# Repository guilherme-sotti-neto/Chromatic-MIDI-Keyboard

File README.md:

# Chromatic MIDI Button Keyboard 

# About 
This project was made to be open for anyone who wants to make their own Chromatic MIDI Keyboard at home. 
I tried to make it as reliable and fixable as possible.

# Components 
- 1 Arduino Leonardo
- 3 1/4W 220 ohm Resistor
- 3 Buttons 
- 51 Diodes 1N4148 (I recommend them because they are very cheap and overkill for this project)
- 99 MX Hotswap Sockets
- 99 MX 5 Pins Silver Mechanical Switches

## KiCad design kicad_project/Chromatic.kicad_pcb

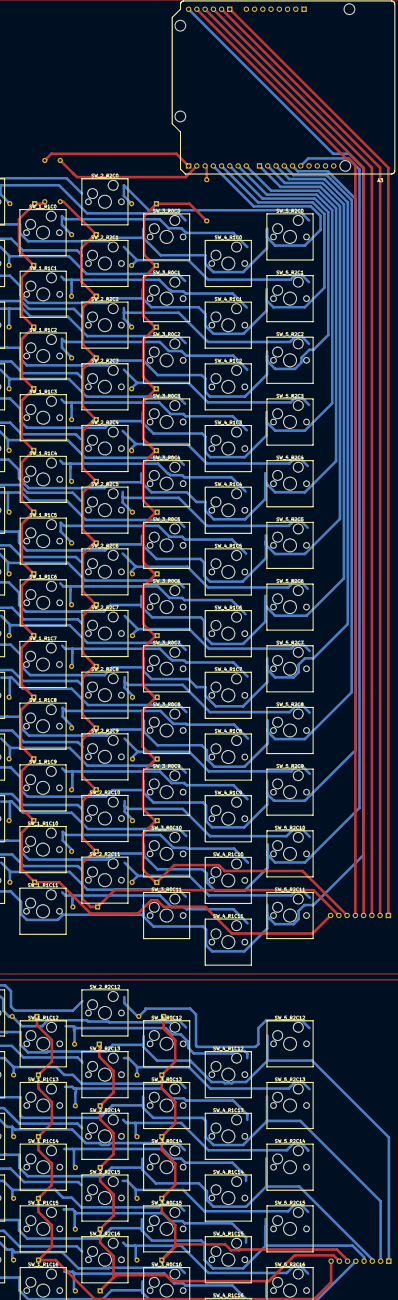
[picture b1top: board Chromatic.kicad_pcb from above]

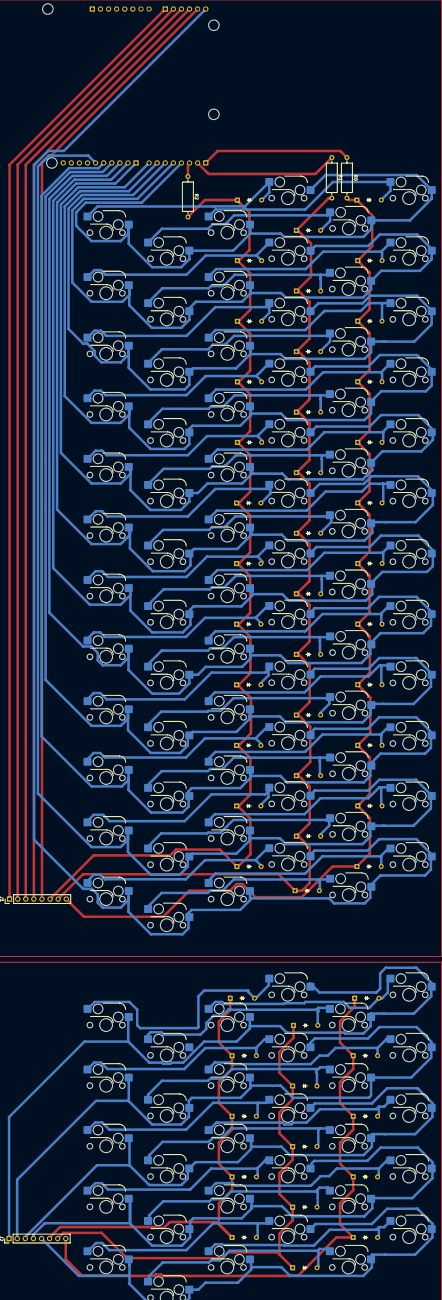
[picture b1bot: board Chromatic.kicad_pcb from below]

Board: 2 copper layers, 159 parts (56 on the bottom side), 82 nets.

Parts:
A3: Arduino_Leonardo_Shield; ARDUINO_A000066
D_R0C0, D_R0C1, D_R0C2, D_R0C3, D_R0C4, D_R0C5, D_R0C6, D_R0C7, D_R0C8, D_R0C9, D_R0C10, D_R0C11, D_R0C12, D_R0C13, D_R0C14, D_R0C15, D_R0C16, D_R1C0, D_R1C1, D_R1C2, D_R1C3, D_R1C4, D_R1C5, D_R1C6, D_R1C7, D_R1C8, D_R1C9, D_R1C10, D_R1C11, D_R1C12, D_R1C13, D_R1C14, D_R1C15, D_R1C16, D_R2C0, D_R2C1, D_R2C2, D_R2C3, D_R2C4, D_R2C5, D_R2C6, D_R2C7, D_R2C8, D_R2C9, D_R2C10, D_R2C11, D_R2C12, D_R2C13, D_R2C14, D_R2C15, D_R2C16: Diode_DO-35
J1: J1; PinHeader_1x08_P2.54mm_Vertical
J2: J2; PinHeader_1x08_P2.54mm_Vertical
R0, R1, R2: Resistor; R_Axial_DIN0309_L9.0mm_D3.2mm_P12.70mm_Horizontal
SW_0_R0C0, SW_0_R0C1, SW_0_R0C2, SW_0_R0C3, SW_0_R0C4, SW_0_R0C5, SW_0_R0C6, SW_0_R0C7, SW_0_R0C8, SW_0_R0C9, SW_0_R0C10, SW_0_R0C11, SW_0_R0C12, SW_0_R0C13, SW_0_R0C14, SW_0_R0C15, SW_0_R0C16, SW_1_R1C0, SW_1_R1C1, SW_1_R1C2, SW_1_R1C3, SW_1_R1C4, SW_1_R1C5, SW_1_R1C6, SW_1_R1C7, SW_1_R1C8, SW_1_R1C9, SW_1_R1C10, SW_1_R1C11, SW_1_R1C12, SW_1_R1C13, SW_1_R1C14, SW_1_R1C15, SW_1_R1C16, SW_2_R2C0, SW_2_R2C1, SW_2_R2C2, SW_2_R2C3, SW_2_R2C4, SW_2_R2C5, SW_2_R2C6, SW_2_R2C7, SW_2_R2C8, SW_2_R2C9, SW_2_R2C10, SW_2_R2C11, SW_2_R2C12, SW_2_R2C13, SW_2_R2C14, SW_2_R2C15, SW_2_R2C16, SW_3_R0C0, SW_3_R0C1, SW_3_R0C2, SW_3_R0C3, SW_3_R0C4, SW_3_R0C5, SW_3_R0C6, SW_3_R0C7, SW_3_R0C8, SW_3_R0C9, SW_3_R0C10, SW_3_R0C11, SW_3_R0C12, SW_3_R0C13, SW_3_R0C14, SW_3_R0C15, SW_3_R0C16, SW_4_R1C0, SW_4_R1C1, SW_4_R1C2, SW_4_R1C3, SW_4_R1C4, SW_4_R1C5, SW_4_R1C6, SW_4_R1C7, SW_4_R1C8, SW_4_R1C9, SW_4_R1C10, SW_4_R1C11, SW_4_R1C12, SW_4_R1C13, SW_4_R1C14, SW_4_R1C15, SW_4_R1C16, SW_5_R2C0, SW_5_R2C1, SW_5_R2C2, SW_5_R2C3, SW_5_R2C4, SW_5_R2C5, SW_5_R2C6, SW_5_R2C7, SW_5_R2C8, SW_5_R2C9, SW_5_R2C10, SW_5_R2C11, SW_5_R2C12, SW_5_R2C13, SW_5_R2C14, SW_5_R2C15, SW_5_R2C16: Keyswitch; Hotswap_MX_1.00u

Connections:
Column 0: A3.D3 (D3_INT0), SW_0_R0C0.1, SW_1_R1C0.1, SW_2_R2C0.1, SW_3_R0C0.1, SW_4_R1C0.1, SW_5_R2C0.1
Column 1: A3.D4, SW_0_R0C1.1, SW_1_R1C1.1, SW_2_R2C1.1, SW_3_R0C1.1, SW_4_R1C1.1, SW_5_R2C1.1
Column 2: A3.D5, SW_0_R0C2.1, SW_1_R1C2.1, SW_2_R2C2.1, SW_3_R0C2.1, SW_4_R1C2.1, SW_5_R2C2.1
Column 3: A3.D6, SW_0_R0C3.1, SW_1_R1C3.1, SW_2_R2C3.1, SW_3_R0C3.1, SW_4_R1C3.1, SW_5_R2C3.1
Column 4: A3.D7 (D7_INT4), SW_0_R0C4.1, SW_1_R1C4.1, SW_2_R2C4.1, SW_3_R0C4.1, SW_4_R1C4.1, SW_5_R2C4.1
Column 5: A3.D8, SW_0_R0C5.1, SW_1_R1C5.1, SW_2_R2C5.1, SW_3_R0C5.1, SW_4_R1C5.1, SW_5_R2C5.1
Column 6: A3.D9, SW_0_R0C6.1, SW_1_R1C6.1, SW_2_R2C6.1, SW_3_R0C6.1, SW_4_R1C6.1, SW_5_R2C6.1
Column 7: A3.D10, SW_0_R0C7.1, SW_1_R1C7.1, SW_2_R2C7.1, SW_3_R0C7.1, SW_4_R1C7.1, SW_5_R2C7.1
Column 8: A3.D11, SW_0_R0C8.1, SW_1_R1C8.1, SW_2_R2C8.1, SW_3_R0C8.1, SW_4_R1C8.1, SW_5_R2C8.1
Column 9: A3.D12, SW_0_R0C9.1, SW_1_R1C9.1, SW_2_R2C9.1, SW_3_R0C9.1, SW_4_R1C9.1, SW_5_R2C9.1
Column 10: A3.D13, SW_0_R0C10.1, SW_1_R1C10.1, SW_2_R2C10.1, SW_3_R0C10.1, SW_4_R1C10.1, SW_5_R2C10.1
Column 11: A3.A5, SW_0_R0C11.1, SW_1_R1C11.1, SW_2_R2C11.1, SW_3_R0C11.1, SW_4_R1C11.1, SW_5_R2C11.1
Column 12: A3.A0, J1.1
Column 13: A3.A1, J1.2
Column 14: A3.A2, J1.3
Column 15: A3.A3, J1.4
Column 16: A3.A4, J1.5
D_R0C11: D_R0C0.1 (K), D_R0C1.1 (K), D_R0C2.1 (K), D_R0C3.1 (K), D_R0C4.1 (K), D_R0C5.1 (K), D_R0C6.1 (K), D_R0C7.1 (K), D_R0C8.1 (K), D_R0C9.1 (K), D_R0C10.1 (K), D_R0C11.1 (K), J1.8, R0.2
D_R1C11: D_R1C0.1 (K), D_R1C1.1 (K), D_R1C2.1 (K), D_R1C3.1 (K), D_R1C4.1 (K), D_R1C5.1 (K), D_R1C6.1 (K), D_R1C7.1 (K), D_R1C8.1 (K), D_R1C9.1 (K), D_R1C10.1 (K), D_R1C11.1 (K), J1.7, R1.2
D_R2C11: D_R2C0.1 (K), D_R2C1.1 (K), D_R2C2.1 (K), D_R2C3.1 (K), D_R2C4.1 (K), D_R2C5.1 (K), D_R2C6.1 (K), D_R2C7.1 (K), D_R2C8.1 (K), D_R2C9.1 (K), D_R2C10.1 (K), D_R2C11.1 (K), J1.6, R2.2
unnamed: D_R0C0.2 (A), SW_0_R0C0.2, SW_3_R0C0.2
unnamed: D_R0C1.2 (A), SW_0_R0C1.2, SW_3_R0C1.2
unnamed: D_R0C2.2 (A), SW_0_R0C2.2, SW_3_R0C2.2
unnamed: D_R0C3.2 (A), SW_0_R0C3.2, SW_3_R0C3.2
unnamed: D_R0C4.2 (A), SW_0_R0C4.2, SW_3_R0C4.2
unnamed: D_R0C5.2 (A), SW_0_R0C5.2, SW_3_R0C5.2
unnamed: D_R0C6.2 (A), SW_0_R0C6.2, SW_3_R0C6.2
unnamed: D_R0C7.2 (A), SW_0_R0C7.2, SW_3_R0C7.2
unnamed: D_R0C8.2 (A), SW_0_R0C8.2, SW_3_R0C8.2
unnamed: D_R0C9.2 (A), SW_0_R0C9.2, SW_3_R0C9.2
unnamed: D_R0C10.2 (A), SW_0_R0C10.2, SW_3_R0C10.2
unnamed: D_R0C11.2 (A), SW_0_R0C11.2, SW_3_R0C11.2
unnamed: D_R0C12.2 (A), SW_0_R0C12.2, SW_3_R0C12.2
unnamed: D_R0C12.1 (K), D_R0C13.1 (K), D_R0C14.1 (K), D_R0C15.1 (K), D_R0C16.1 (K), J2.8
unnamed: D_R0C13.2 (A), SW_0_R0C13.2, SW_3_R0C13.2
unnamed: D_R0C14.2 (A), SW_0_R0C14.2, SW_3_R0C14.2
unnamed: D_R0C15.2 (A), SW_0_R0C15.2, SW_3_R0C15.2
unnamed: D_R0C16.2 (A), SW_0_R0C16.2, SW_3_R0C16.2
unnamed: D_R1C0.2 (A), SW_1_R1C0.2, SW_4_R1C0.2
unnamed: D_R1C1.2 (A), SW_1_R1C1.2, SW_4_R1C1.2
unnamed: D_R1C2.2 (A), SW_1_R1C2.2, SW_4_R1C2.2
unnamed: D_R1C3.2 (A), SW_1_R1C3.2, SW_4_R1C3.2
unnamed: D_R1C4.2 (A), SW_1_R1C4.2, SW_4_R1C4.2
unnamed: D_R1C5.2 (A), SW_1_R1C5.2, SW_4_R1C5.2
unnamed: D_R1C6.2 (A), SW_1_R1C6.2, SW_4_R1C6.2
unnamed: D_R1C7.2 (A), SW_1_R1C7.2, SW_4_R1C7.2
unnamed: D_R1C8.2 (A), SW_1_R1C8.2, SW_4_R1C8.2
unnamed: D_R1C9.2 (A), SW_1_R1C9.2, SW_4_R1C9.2
unnamed: D_R1C10.2 (A), SW_1_R1C10.2, SW_4_R1C10.2
unnamed: D_R1C11.2 (A), SW_1_R1C11.2, SW_4_R1C11.2
unnamed: D_R1C12.2 (A), SW_1_R1C12.2, SW_4_R1C12.2
unnamed: D_R1C12.1 (K), D_R1C13.1 (K), D_R1C14.1 (K), D_R1C15.1 (K), D_R1C16.1 (K), J2.7
unnamed: D_R1C13.2 (A), SW_1_R1C13.2, SW_4_R1C13.2
unnamed: D_R1C14.2 (A), SW_1_R1C14.2, SW_4_R1C14.2
unnamed: D_R1C15.2 (A), SW_1_R1C15.2, SW_4_R1C15.2
unnamed: D_R1C16.2 (A), SW_1_R1C16.2, SW_4_R1C16.2
unnamed: D_R2C0.2 (A), SW_2_R2C0.2, SW_5_R2C0.2
unnamed: D_R2C1.2 (A), SW_2_R2C1.2, SW_5_R2C1.2
unnamed: D_R2C2.2 (A), SW_2_R2C2.2, SW_5_R2C2.2
unnamed: D_R2C3.2 (A), SW_2_R2C3.2, SW_5_R2C3.2
unnamed: D_R2C4.2 (A), SW_2_R2C4.2, SW_5_R2C4.2
unnamed: D_R2C5.2 (A), SW_2_R2C5.2, SW_5_R2C5.2
unnamed: D_R2C6.2 (A), SW_2_R2C6.2, SW_5_R2C6.2
unnamed: D_R2C7.2 (A), SW_2_R2C7.2, SW_5_R2C7.2
unnamed: D_R2C8.2 (A), SW_2_R2C8.2, SW_5_R2C8.2
unnamed: D_R2C9.2 (A), SW_2_R2C9.2, SW_5_R2C9.2
unnamed: D_R2C10.2 (A), SW_2_R2C10.2, SW_5_R2C10.2
unnamed: D_R2C11.2 (A), SW_2_R2C11.2, SW_5_R2C11.2
unnamed: D_R2C12.2 (A), SW_2_R2C12.2, SW_5_R2C12.2
unnamed: D_R2C12.1 (K), D_R2C13.1 (K), D_R2C14.1 (K), D_R2C15.1 (K), D_R2C16.1 (K), J2.6
unnamed: D_R2C13.2 (A), SW_2_R2C13.2, SW_5_R2C13.2
unnamed: D_R2C14.2 (A), SW_2_R2C14.2, SW_5_R2C14.2
unnamed: D_R2C15.2 (A), SW_2_R2C15.2, SW_5_R2C15.2
unnamed: D_R2C16.2 (A), SW_2_R2C16.2, SW_5_R2C16.2
unnamed: J2.1, SW_0_R0C12.1, SW_1_R1C12.1, SW_2_R2C12.1, SW_3_R0C12.1, SW_4_R1C12.1, SW_5_R2C12.1
unnamed: J2.2, SW_0_R0C13.1, SW_1_R1C13.1, SW_2_R2C13.1, SW_3_R0C13.1, SW_4_R1C13.1, SW_5_R2C13.1
unnamed: J2.3, SW_0_R0C14.1, SW_1_R1C14.1, SW_2_R2C14.1, SW_3_R0C14.1, SW_4_R1C14.1, SW_5_R2C14.1
unnamed: J2.4, SW_0_R0C15.1, SW_1_R1C15.1, SW_2_R2C15.1, SW_3_R0C15.1, SW_4_R1C15.1, SW_5_R2C15.1
unnamed: J2.5, SW_0_R0C16.1, SW_1_R1C16.1, SW_2_R2C16.1, SW_3_R0C16.1, SW_4_R1C16.1, SW_5_R2C16.1
Row 0: A3.D0 (D0/RX), R0.1
Row 1: A3.D1 (D1/TX), R1.1
Row 2: A3.D2 (D2_INT1), R2.1

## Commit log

2026-04-19 inicio das coisas
    inicio do esquema e codigo
2026-04-21 teste, pcb, esquema
    codigo de teste criado;
    atualizaçoes no pcb e esquema.
2026-04-21 octave adjust
2026-04-22 doc em ingles
2026-04-24 arrumado
2026-04-26 LAYOUT OK
2026-04-26 footprint
2026-04-26 done
